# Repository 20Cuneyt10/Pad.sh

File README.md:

Hello this is my MacroPad Project. The PCB's all messy and dont even talk about the 3d model which ı havent even done and still need to do in the near future. 
V1 of Pad.sh

V2 of Pad.sh

on the V2 placement of the switches are hopefully fixed ı am still seeing some issues but dont know how to fix them i tried making the pcb bigger but still same issue.

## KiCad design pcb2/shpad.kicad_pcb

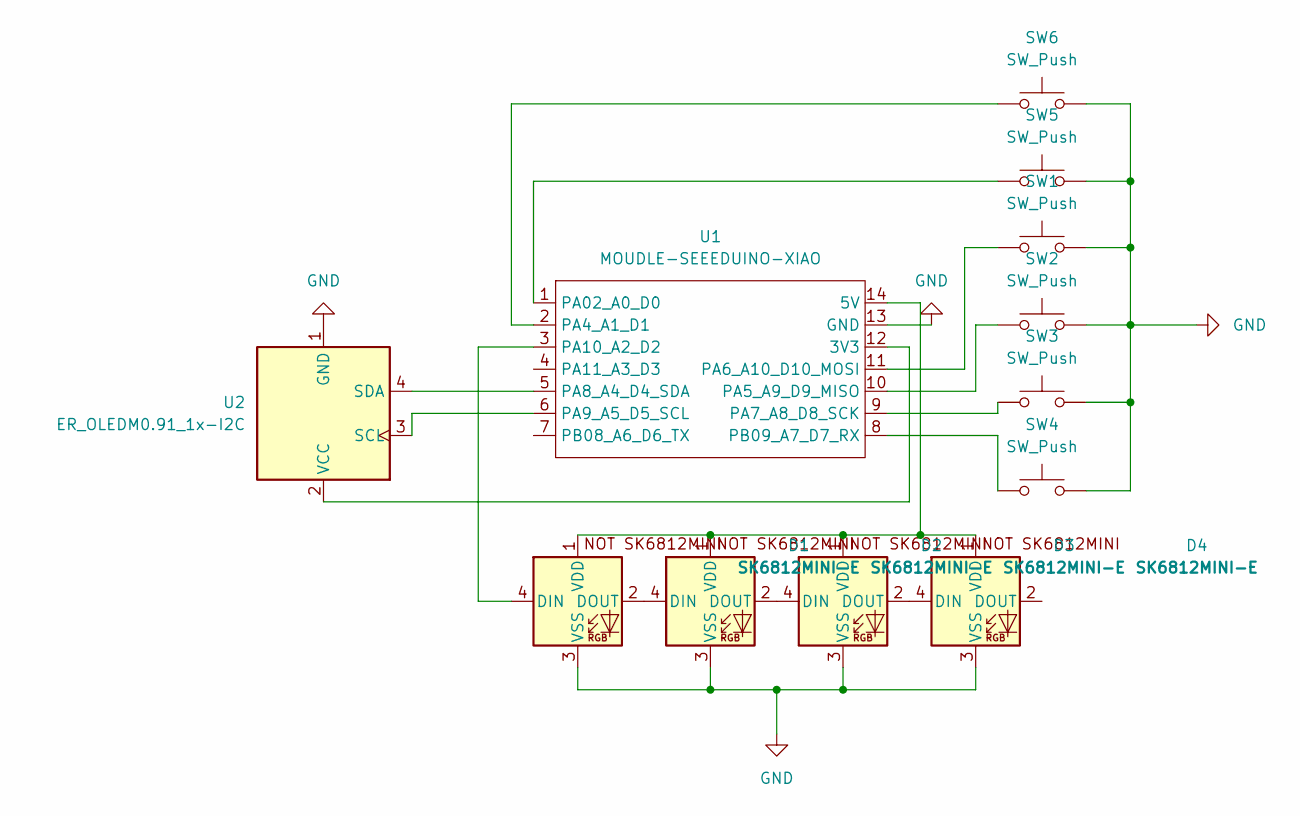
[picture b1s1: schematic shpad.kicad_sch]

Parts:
D1, D2, D3, D4: SK6812MINI-E; SK6812MINI-E_fixed
SW1, SW2, SW3, SW4, SW5, SW6: SW_Push; MX-Hotswap-1U
U1: MOUDLE-SEEEDUINO-XIAO; XIAO-Generic-Hybrid-14P-2.54-21X17.8MM
U2: ER_OLEDM0.91_1x-I2C

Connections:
GND: D1.3 (VSS), D2.3 (VSS), D3.3 (VSS), D4.3 (VSS), SW1.2, SW2.2, SW3.2, SW4.2, SW5.2, SW6.2, U1.13 (GND), U2.1 (GND)
unnamed: D1.4 (DIN), U1.3 (PA10_A2_D2)
unnamed: D1.2 (DOUT), D2.4 (DIN)
unnamed: D1.1 (VDD), D2.1 (VDD), D3.1 (VDD), D4.1 (VDD), U1.14 (5V)
unnamed: D2.2 (DOUT), D3.4 (DIN)
unnamed: D3.2 (DOUT), D4.4 (DIN)
unnamed: U1.12 (3V3), U2.2 (VCC)
unnamed: SW5.1, U1.1 (PA02_A0_D0)
unnamed: SW6.1, U1.2 (PA4_A1_D1)
unnamed: SW2.1, U1.10 (PA5_A9_D9_MISO)
unnamed: SW1.1, U1.11 (PA6_A10_D10_MOSI)
unnamed: SW3.1, U1.9 (PA7_A8_D8_SCK)
unnamed: U1.5 (PA8_A4_D4_SDA), U2.4 (SDA)
unnamed: U1.6 (PA9_A5_D5_SCL), U2.3 (SCL)
unnamed: SW4.1, U1.8 (PB09_A7_D7_RX)

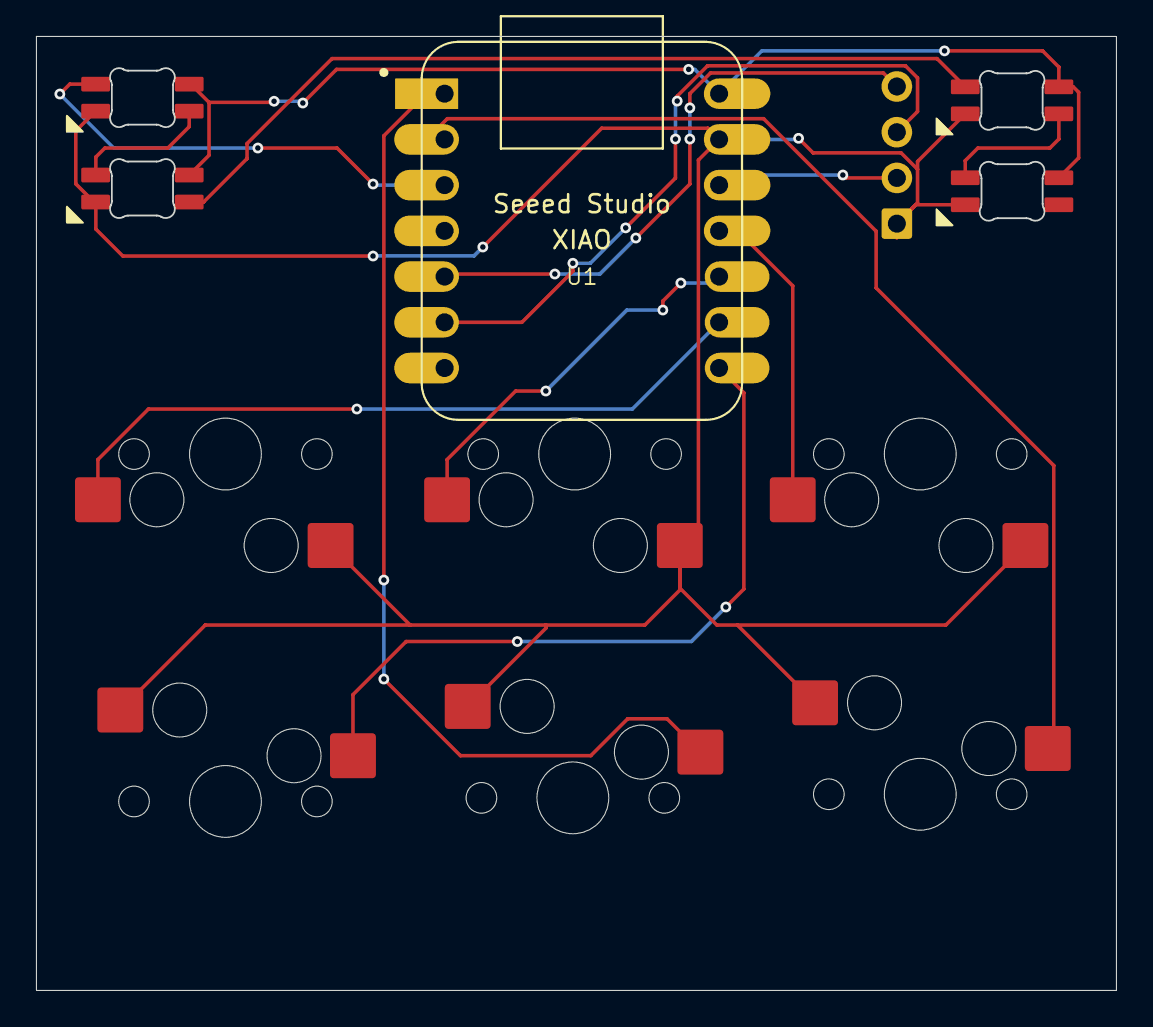
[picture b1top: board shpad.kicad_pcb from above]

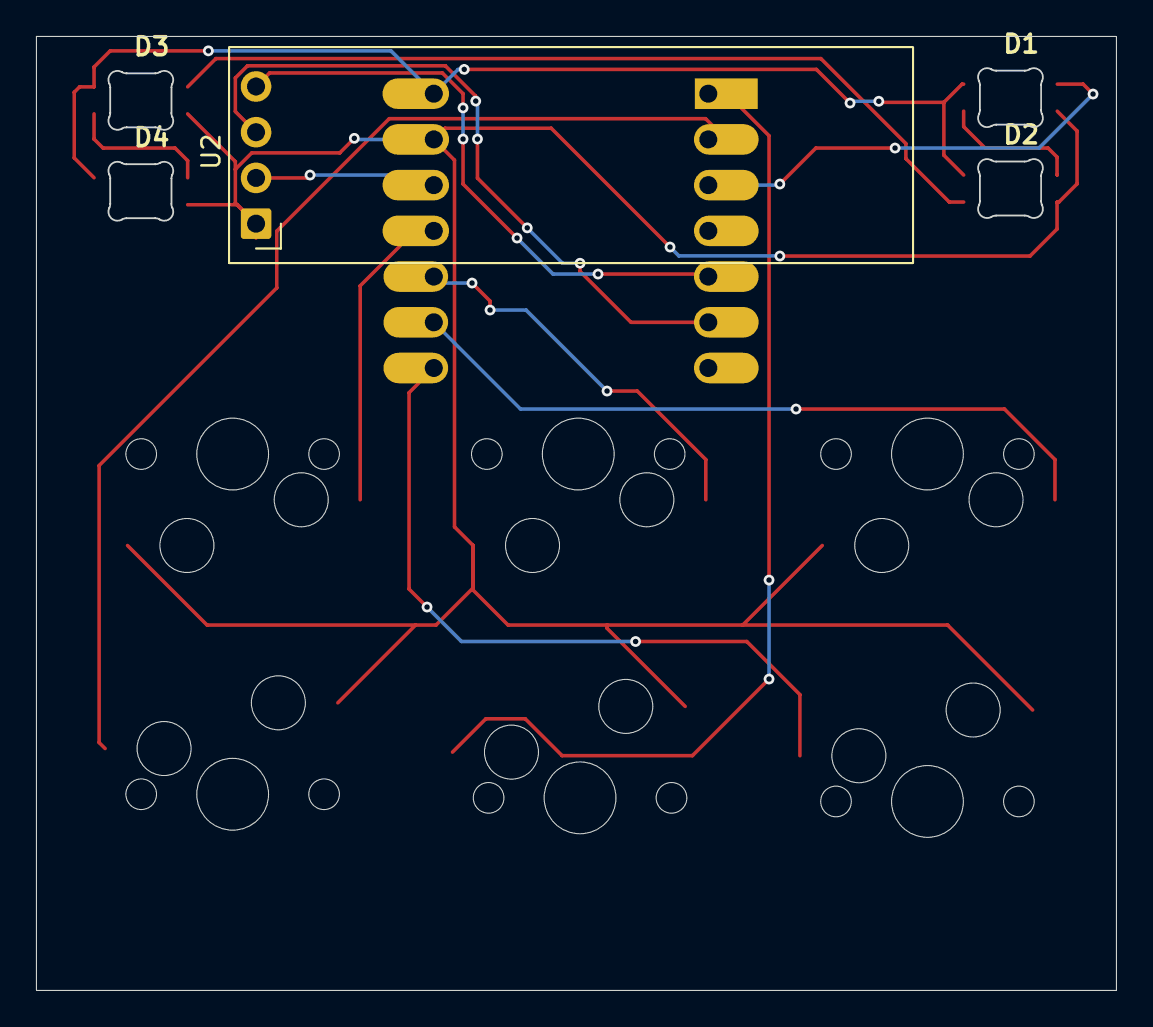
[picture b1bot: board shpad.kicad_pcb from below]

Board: 2 copper layers, 60.0 x 53.0 mm, 12 parts (5 on the bottom side), 15 nets.

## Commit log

2026-06-11 uploading pcb desings 1 incomplete and 2 complete
2026-06-12 Added the first 2 pcbs
2026-06-12 Added images, added improved V2 of shpad edited readme
2026-06-12 relocated text
2026-06-12 Manufacturing
